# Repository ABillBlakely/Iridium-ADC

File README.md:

# Iridium-ADC
High performance ADC for audio analysis and scientific measurement.

I recommend that you check out the full design document at [docs/Iridium ADC final.pdf](docs/Iridium%20ADC%20final.pdf). 

That very large document contains schematics, gerbers, BOMs, performance metrics, motivations, and analysis.

## Repository
This repository is organized by folder structure.

* docs: contains reports and analyses for the project.
* hardware: contains models and information about the physical structure of the project.
* ecad: contains the ecad files including schematic and PCB designs.
* esim: contains electronic simulation files.
* src: source files for STM32F446RE microcontroller.

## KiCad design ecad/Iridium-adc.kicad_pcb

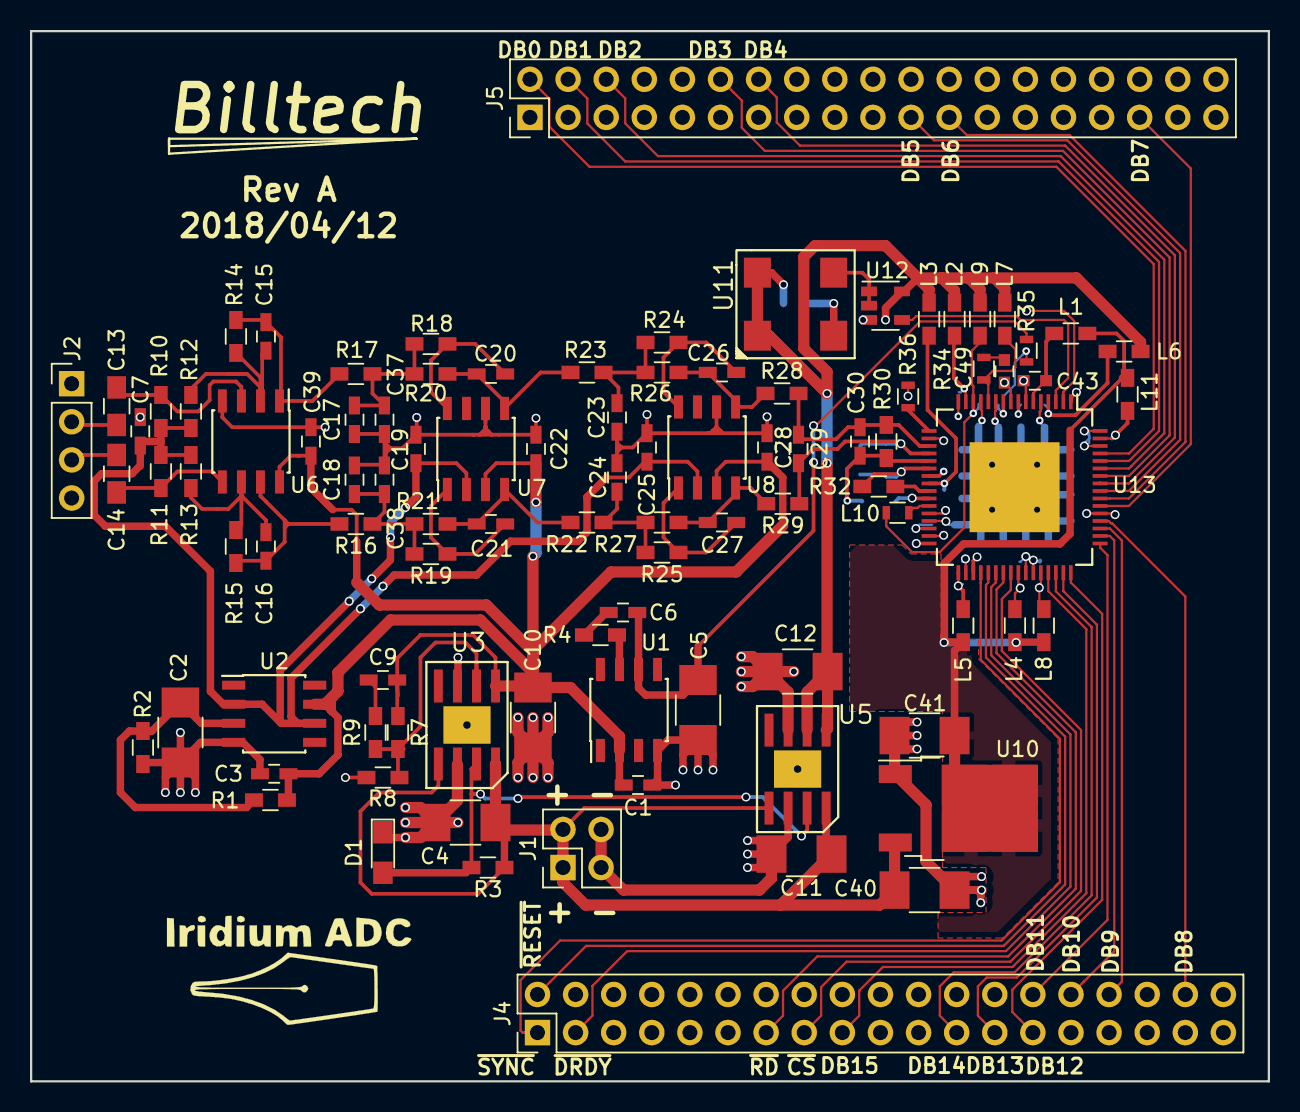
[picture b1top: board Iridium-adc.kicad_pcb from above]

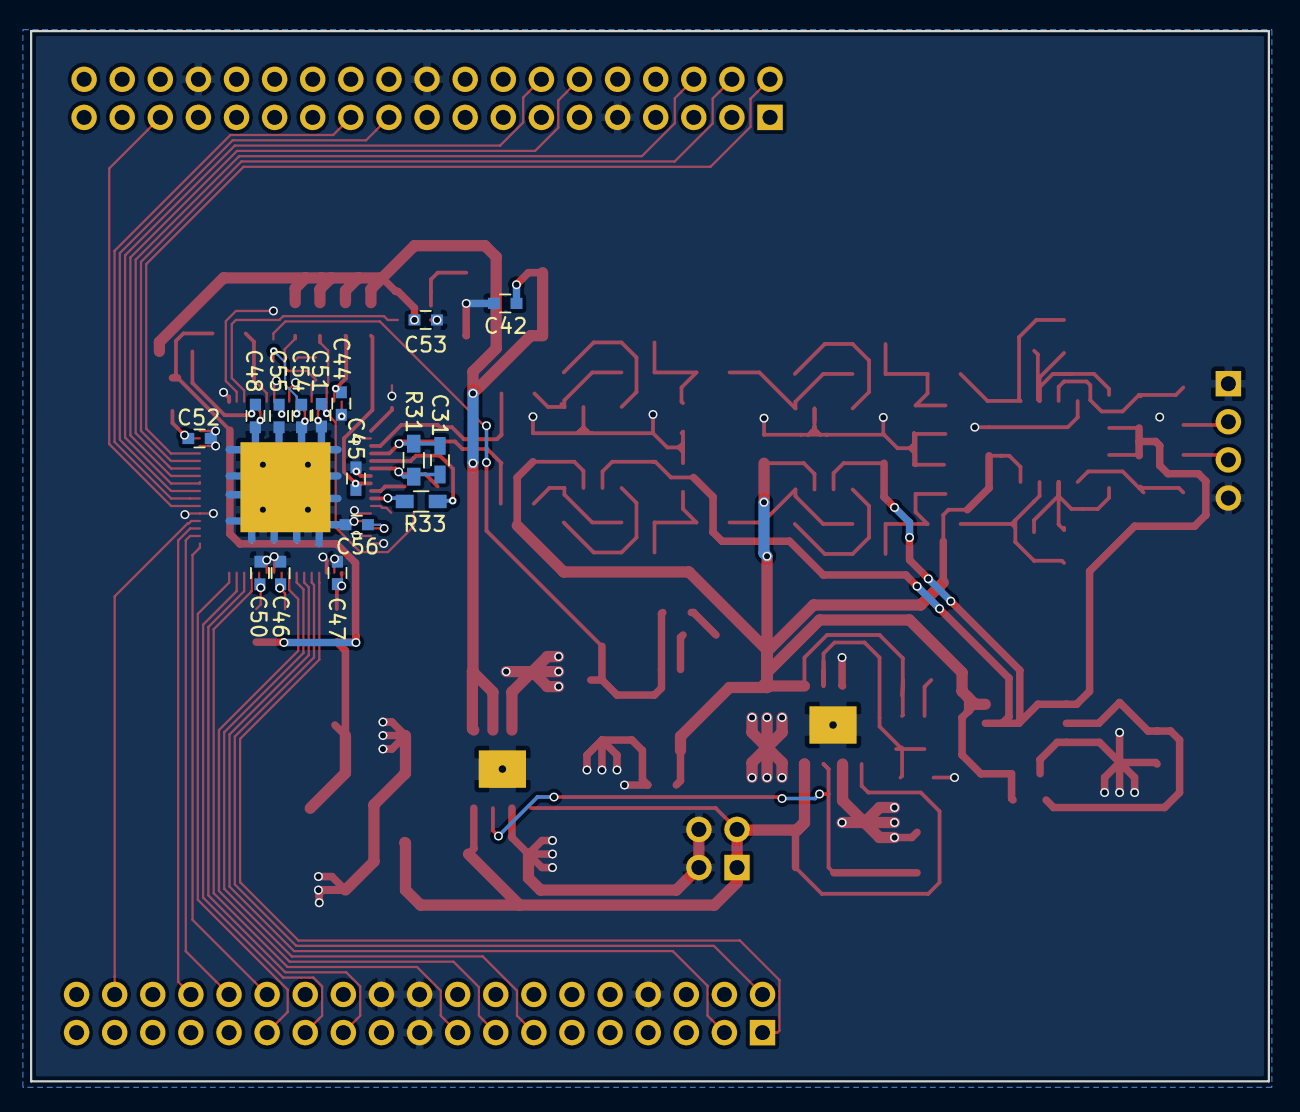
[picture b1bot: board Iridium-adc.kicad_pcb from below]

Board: 2 copper layers, 82.5 x 70.0 mm, 111 parts (16 on the bottom side), 78 nets.

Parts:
C1, C3, C7, C19, C22, C25, C28, C39: 0.1u; C_0603_HandSoldering
C2, C4, C5, C10, C11, C12, C40, C41: 22u; C_1210_HandSoldering
C6: 10n; C_0603_HandSoldering
C9: 39n; C_0603_HandSoldering
C13, C14: 2.2u; C_0805_HandSoldering
C15, C16: 47p; C_0603_HandSoldering
C17, C18: 220p; C_0603_HandSoldering
C20, C21, C26, C27, C29: 100p; C_0603_HandSoldering
C23, C24: 1.5n; C_0603_HandSoldering
C30, C31: 120p; C_0603_HandSoldering
C37, C38: 20p; C_0603_HandSoldering
C42, C43, C44, C45, C46, C47, C48, C50, C51, C52, C53, C55: 0.1u; C_0603
C49, C54: 10n; C_0603
C56: 33p; C_0603
D1: LED; LED_0805_HandSoldering
J1: +15V; Pin_Header_Straight_2x02_Pitch2.54mm
J2: XLR3; Pin_Header_Straight_1x04_Pitch2.54mm
J4: Nucleo_F446_LHS; Pin_Header_Straight_2x19_Pitch2.54mm
J5: Nucleo_F446_RHS; Pin_Header_Straight_2x19_Pitch2.54mm
L1, L2, L3, L4, L5, L6, L7, L8, L9, L11: 1k@100M; L_0603_HandSoldering
L10: 15n; L_0603
R1, R2, R3, R8, R9: 10k; R_0603_HandSoldering
R4: 82k; R_0603_HandSoldering
R7: 86k6; R_0603_HandSoldering
R10, R11: 1M; R_0603_HandSoldering
R12, R13, R14, R15: 349; R_0603_HandSoldering
R16, R17, R20, R21: 1k05; R_0603_HandSoldering
R18, R19: 698; R_0603_HandSoldering
R22, R23: 367; R_0603_HandSoldering
R24, R25: 332; R_0603_HandSoldering
R26, R27: 220; R_0603_HandSoldering
R28, R29: 1k; R_0603_HandSoldering
R30, R31: 655; R_0603_HandSoldering
R32, R33: 18; R_0603_HandSoldering
R34, R35: 10; R_0603
R36: 160k; R_0603
U1: ADR434BRZ; SOIC-8_3.9x4.9mm_Pitch1.27mm
U2: OPA207IDR; SOIC-8_3.9x4.9mm_Pitch1.27mm
U3: ADP7105ARDZ; SOIC-8-EP
U5: ADP7104ARDZ-5.0; SOIC-8-EP
U6: OPA1612; SOIC-8_3.9x4.9mm_Pitch1.27mm
U7, U8: OPA1632; SOIC-8_3.9x4.9mm_Pitch1.27mm
U10: NCV1117ST25T3G; TO-252-2
U11: CB3-3C-40M0000; CTS_CB3_oscillator
U12: NC7SZ08M5; SOT-23-5
U13: AD7760; LQFP-EP-64_10x10mm_Pitch0.5mm_6mm_square_paddle

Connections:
+2V5: C41.1, L1.1, L4.1, L5.1, L8.1, L11.1, U10.2
+5V: C12.1, C42.1, C53.1, L2.1, L3.1, L6.1, L7.1, L9.1, U5.1, U5.2, U11.1, U11.4, U12.5
+12V: C1.1, C3.2, C9.1, C10.1, C22.1, C28.1, C39.1, R1.1, R7.1, U1.2, U2.7, U3.1, U6.8, U7.3, U8.3
+15V: C4.1, C11.1, C40.1, J1.1, J1.2, R3.1, U3.5, U3.8, U5.5, U5.8, U10.3
/ADC/4.096: C5.1, C6.2, R35.2, U1.6
/ADC/DB0: J5.2, U13.61
/ADC/DB1: J5.4, U13.60
/ADC/DB2: J5.6, U13.59
/ADC/DB3: J5.12, U13.58
/ADC/DB4: J5.14, U13.57
/ADC/DB5: J5.21, U13.56
/ADC/DB6: J5.23, U13.55
/ADC/DB7: J5.33, U13.54
/ADC/DB8: J4.36, U13.52
/ADC/DB9: J4.32, U13.51
/ADC/DB10: J4.30, U13.50
/ADC/DB11: J4.28, U13.49
/ADC/DB12: J4.27, U13.48
/ADC/DB13: J4.25, U13.47
/ADC/DB14: J4.23, U13.46
/ADC/DB15: J4.17, U13.45
/ADC/InputN: C27.1, R27.1, R29.2, U8.4
/ADC/InputP: C26.1, R26.1, R28.2, U8.5
/ADC/MCLK: U12.4, U13.3
/ADC/Pin4(RHS): C48.1, L6.2, U13.4
/ADC/Pin6(Vmod1): C43.1, L1.2, U13.6
/ADC/Pin10(VRefP): C54.1, R35.1, U13.10
/ADC/Pin12(Vbuf): L7.2, R34.1, U13.12
/ADC/Pin14(LHS): C51.1, L9.2, L10.1, U13.14
/ADC/Pin15(Vbias): C44.1, L2.2, U13.15
/ADC/Pin24(VDif1): C45.1, L3.2, U13.24
/ADC/Pin27: L10.2, U13.27
/ADC/Pin33(Vmod2): C47.1, L5.2, U13.33
/ADC/Pin41(DVdd): C46.1, L4.2, U13.41
/ADC/Pin44(Vdrive1): C50.1, L8.2, U13.44
/ADC/Pin63(Vdrive2): C52.1, L11.2, U13.63
/ADC/VINAN: C29.1, C31.2, R29.1, R31.2, U13.20
/ADC/VINAP: C29.2, C30.2, R28.1, R30.2, U13.19
/ADC/VINN: R33.1, U13.26
/ADC/VINP: R32.1, U13.25
/ADC/VOUTAN: C30.1, R30.1, R33.2, U13.21
/ADC/VOUTAP: C31.1, R31.1, R32.2, U13.22
/ADC/~CS: J4.15, U13.40
/ADC/~DRDY: J4.3, U13.38
/ADC/~RD: J4.13, U13.39
/ADC/~RESET: J4.2, U13.37
/ADC/~SYNC: J4.1, U13.36
/Input/BIAS: C7.1, C19.1, C25.1, R10.2, R11.1, R12.1, R13.1, U2.2, U2.6, U7.2, U8.2
GND: C1.2, C2.2, C3.1, C4.2, C5.2, C7.2, C10.2, C11.2, C12.2, C17.2, C18.2, C19.2, C22.2, C23.2, C24.2, C25.2, C28.2, C37.2, C38.2, C39.2, C40.2, C41.2, C42.2, C43.2, C44.2, C45.2, C46.2, C47.2, C48.2, C49.2, C50.2, C51.2, C52.2, C53.2, C54.2, C55.2, C56.2, D1.1, J1.3, J1.4, J2.1, J2.4, J4.8, J4.19, J4.20, J4.22, J5.9, J5.20, J5.32, R2.2, R8.2, R36.2, U1.4, U2.4, U3.3, U3.6, U3.9, U5.3, U5.6, U5.9, U6.4, U7.6, U8.6, U10.1, U11.2, U12.3, U13.1, U13.2, U13.5, U13.7, U13.9, U13.11, U13.13, U13.16, U13.18, U13.23, U13.28, U13.29, U13.31, U13.32, U13.34, U13.35, U13.42, U13.43, U13.53, U13.62, U13.64, U13.65
unnamed: C2.1, R1.2, R2.1, U2.3
unnamed: C6.1, R4.1
unnamed: C9.2, R9.1
unnamed: C13.1, R10.1, U6.3
unnamed: C13.2, J2.2
unnamed: C14.1, R11.2, U6.5
unnamed: C14.2, J2.3
unnamed: C15.1, R14.1, R17.2, U6.1
unnamed: C15.2, R12.2, R14.2, U6.2
unnamed: C16.1, R15.1, R16.2, U6.7
unnamed: C16.2, R13.2, R15.2, U6.6
unnamed: C17.1, C37.1, R17.1, R18.2, R20.2
unnamed: C18.1, C38.1, R16.1, R19.2, R21.2
unnamed: C20.1, R20.1, R23.2, U7.5
unnamed: C20.2, R18.1, U7.8
unnamed: C21.1, R21.1, R22.2, U7.4
unnamed: C21.2, R19.1, U7.1
unnamed: C23.1, R23.1, R24.2, R26.2
unnamed: C24.1, R22.1, R25.2, R27.2
unnamed: C26.2, R24.1, U8.8
unnamed: C27.2, R25.1, U8.1
unnamed: C49.1, R34.2
unnamed: C55.1, U13.8
unnamed: C56.1, U13.30
unnamed: D1.2, R3.2, U3.7, U5.7
unnamed: R4.2, U1.7
unnamed: R7.2, R8.1, R9.2, U3.2
unnamed: R36.1, U13.17
unnamed: U11.3, U12.1, U12.2

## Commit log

2017-12-01 In progress Project Definition and inital 3D Model.
2017-12-01 Remove header underline for markdeep v0.23
2017-12-01 Engineering specs and project analysis added.
2017-12-02 Full Report first draft.
2017-12-12 Break sections up into individual files and run language tool on each section.
2018-02-05 Setup environment for mbed RTOS
2018-02-23 Clean and organize directory a little.
2018-02-23 Restructure src file, clean directory, update readme and src\readme
2018-02-24 Working test of SPI2 interface.
2018-04-04 Mostly complete schematic, about to tape out the PCB.
2018-04-04 Minor simulation changes to reflect the implementation.
2018-04-11 First complete pass of PCB with preamp, ADC, and nucleo dev board connections.
2018-04-13 Rev A of board as ordered from Osh Park.
2018-04-18 build some test to verify pins of dev board.
2018-04-20 Write initialization routine (untested), move pin defs to own file.
2018-04-20 Source track binary file.
2018-04-24 Write function to efficiently use the databus and use an interruppt on the ~DRDY pin. UNTESTED
2018-04-25 Working sampling in need of performance improvements.
2018-04-25 Remove port detanglement, 560 k -> 860k
2018-04-25 Sort out all necessary pin changes.
2018-04-25 Add logo file to git.
2018-04-25 Change body font size from % to px.
2018-04-25 Matlab file simulating sample data and the effects of quantization and noise.
2018-04-25 set sample array as volatile, reinstate data disentaglement. This should be considered the starting performance benchmark at 570 kSPS.
2018-04-25 Optimize read detangle 570k -> 617 kSPS.
2018-04-25 Switch strategies from disentagle to efficient packing. 745 kSPS
2018-04-25 Ever so slightly more efficient read function. 764 kSPS
2018-05-08 mbed directory clean up, configure for merge to main branch and testing of board.
2018-05-08 Correct part name from adp7104 to adp7105, which has a soft start feature.
2018-05-08 moves lines from clear_terminal back to collect_samples where they belonged.
2018-05-08 Fix status register display to show decimation as a single decimal value.
2018-05-08 Change pin from pc_7 to pa_5
2018-05-09 Writing to buffer appears to be correct code but decimation rate setting is not functional.
2018-05-10 Sampling is happening, not sure if it is happening correctly yet.
2018-05-10 Create a class structure for the adc functions.
2018-05-11 term control attempt not working.
2018-05-11 Functional sampling almost ready for interface with PC.
2018-05-15 Python gui using dash and plotly to view and control the adc.
2018-05-15 Interface and interaction improvements, including fft size and windowing selection.
2018-05-16 Attempts to change the decimation rate in the UI have led to this point.
2018-05-16 A new approach to communication using two way signaling. Not currently working
2018-05-17 Running stably at 115200 baud. Decimation switch untested."
2018-05-17 Working at 2 Mbps baud rate. Removed some unnecessary print and other statements.
2018-05-19 Change Pin PA5 to PC7. Create two way communication scheme. UNTESTED
2018-05-19 Add logging and performance measures.
2018-05-20 Apparently functioning two way communication, but incredibly slow.
2018-05-21 Tweak the MCU code to operate on poll instead of interrupt
2018-05-21 Back to interrupt driven, polling misses some events. The delay adding in between data bus reads was the critical component. Reliably working sampling now.
2018-05-22 Approximate scaling, removal of mean, baud rate = 1500000 seems to be majical for now.
2018-05-22 Minor changes incl. longer buffer size. Operation very stable.
2018-05-22 Simulation agrees that the input range is less than required to overload the adc input. This is due to forgetting the factor of two in the differential signals during desing, so each attenuation is a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
2018-05-22 Move to propagation updates instead of entirely timer driven.
2018-05-23 index on (no branch): b7848d86 Minor changes incl. longer buffer size. Operation very stable.
2018-05-23 scale windows correctly, hide decimation selection while it is not working.
2018-05-25 Hardware changes for bias voltage osc fix and planned preamp gain correction part selection.
2018-05-25 Various quality of life improvements.
2018-05-25 storing becuase windows.
2018-05-25 Approx DC offset and scale factor set.
2018-05-25 Add button to show the window in the time domain graph.
2018-05-28 Restructure GUI, implement sample rate and number of sample switchability.
2018-05-30 Remove errant sim file.
2018-05-30 Revision of background, more work required in this section.
2018-05-30 Revise overview of need
2018-05-30 Revise customer needs
2018-05-30 Revise market decscription. This section should be heavily revised or just removed.
2018-06-01 Market req's reviewed, will probably be removed or heavily modified later.
2018-06-01 Change fft magnitude to RMS value.
2018-06-04 Slight changes to simulation and ecad with new changes before rollback to old changes.
2018-06-04 commit everything before merge back to main branch.
2018-06-09 Commit it all and let God^H^H^H diff sort it out.
2018-06-09 Final Draft of senior project report done.
2018-06-09 Minor formatting fixes.
2018-06-09 Final draft of senior project report pdf addition.
2023-02-02 Update README.md
    Add link to the final report
